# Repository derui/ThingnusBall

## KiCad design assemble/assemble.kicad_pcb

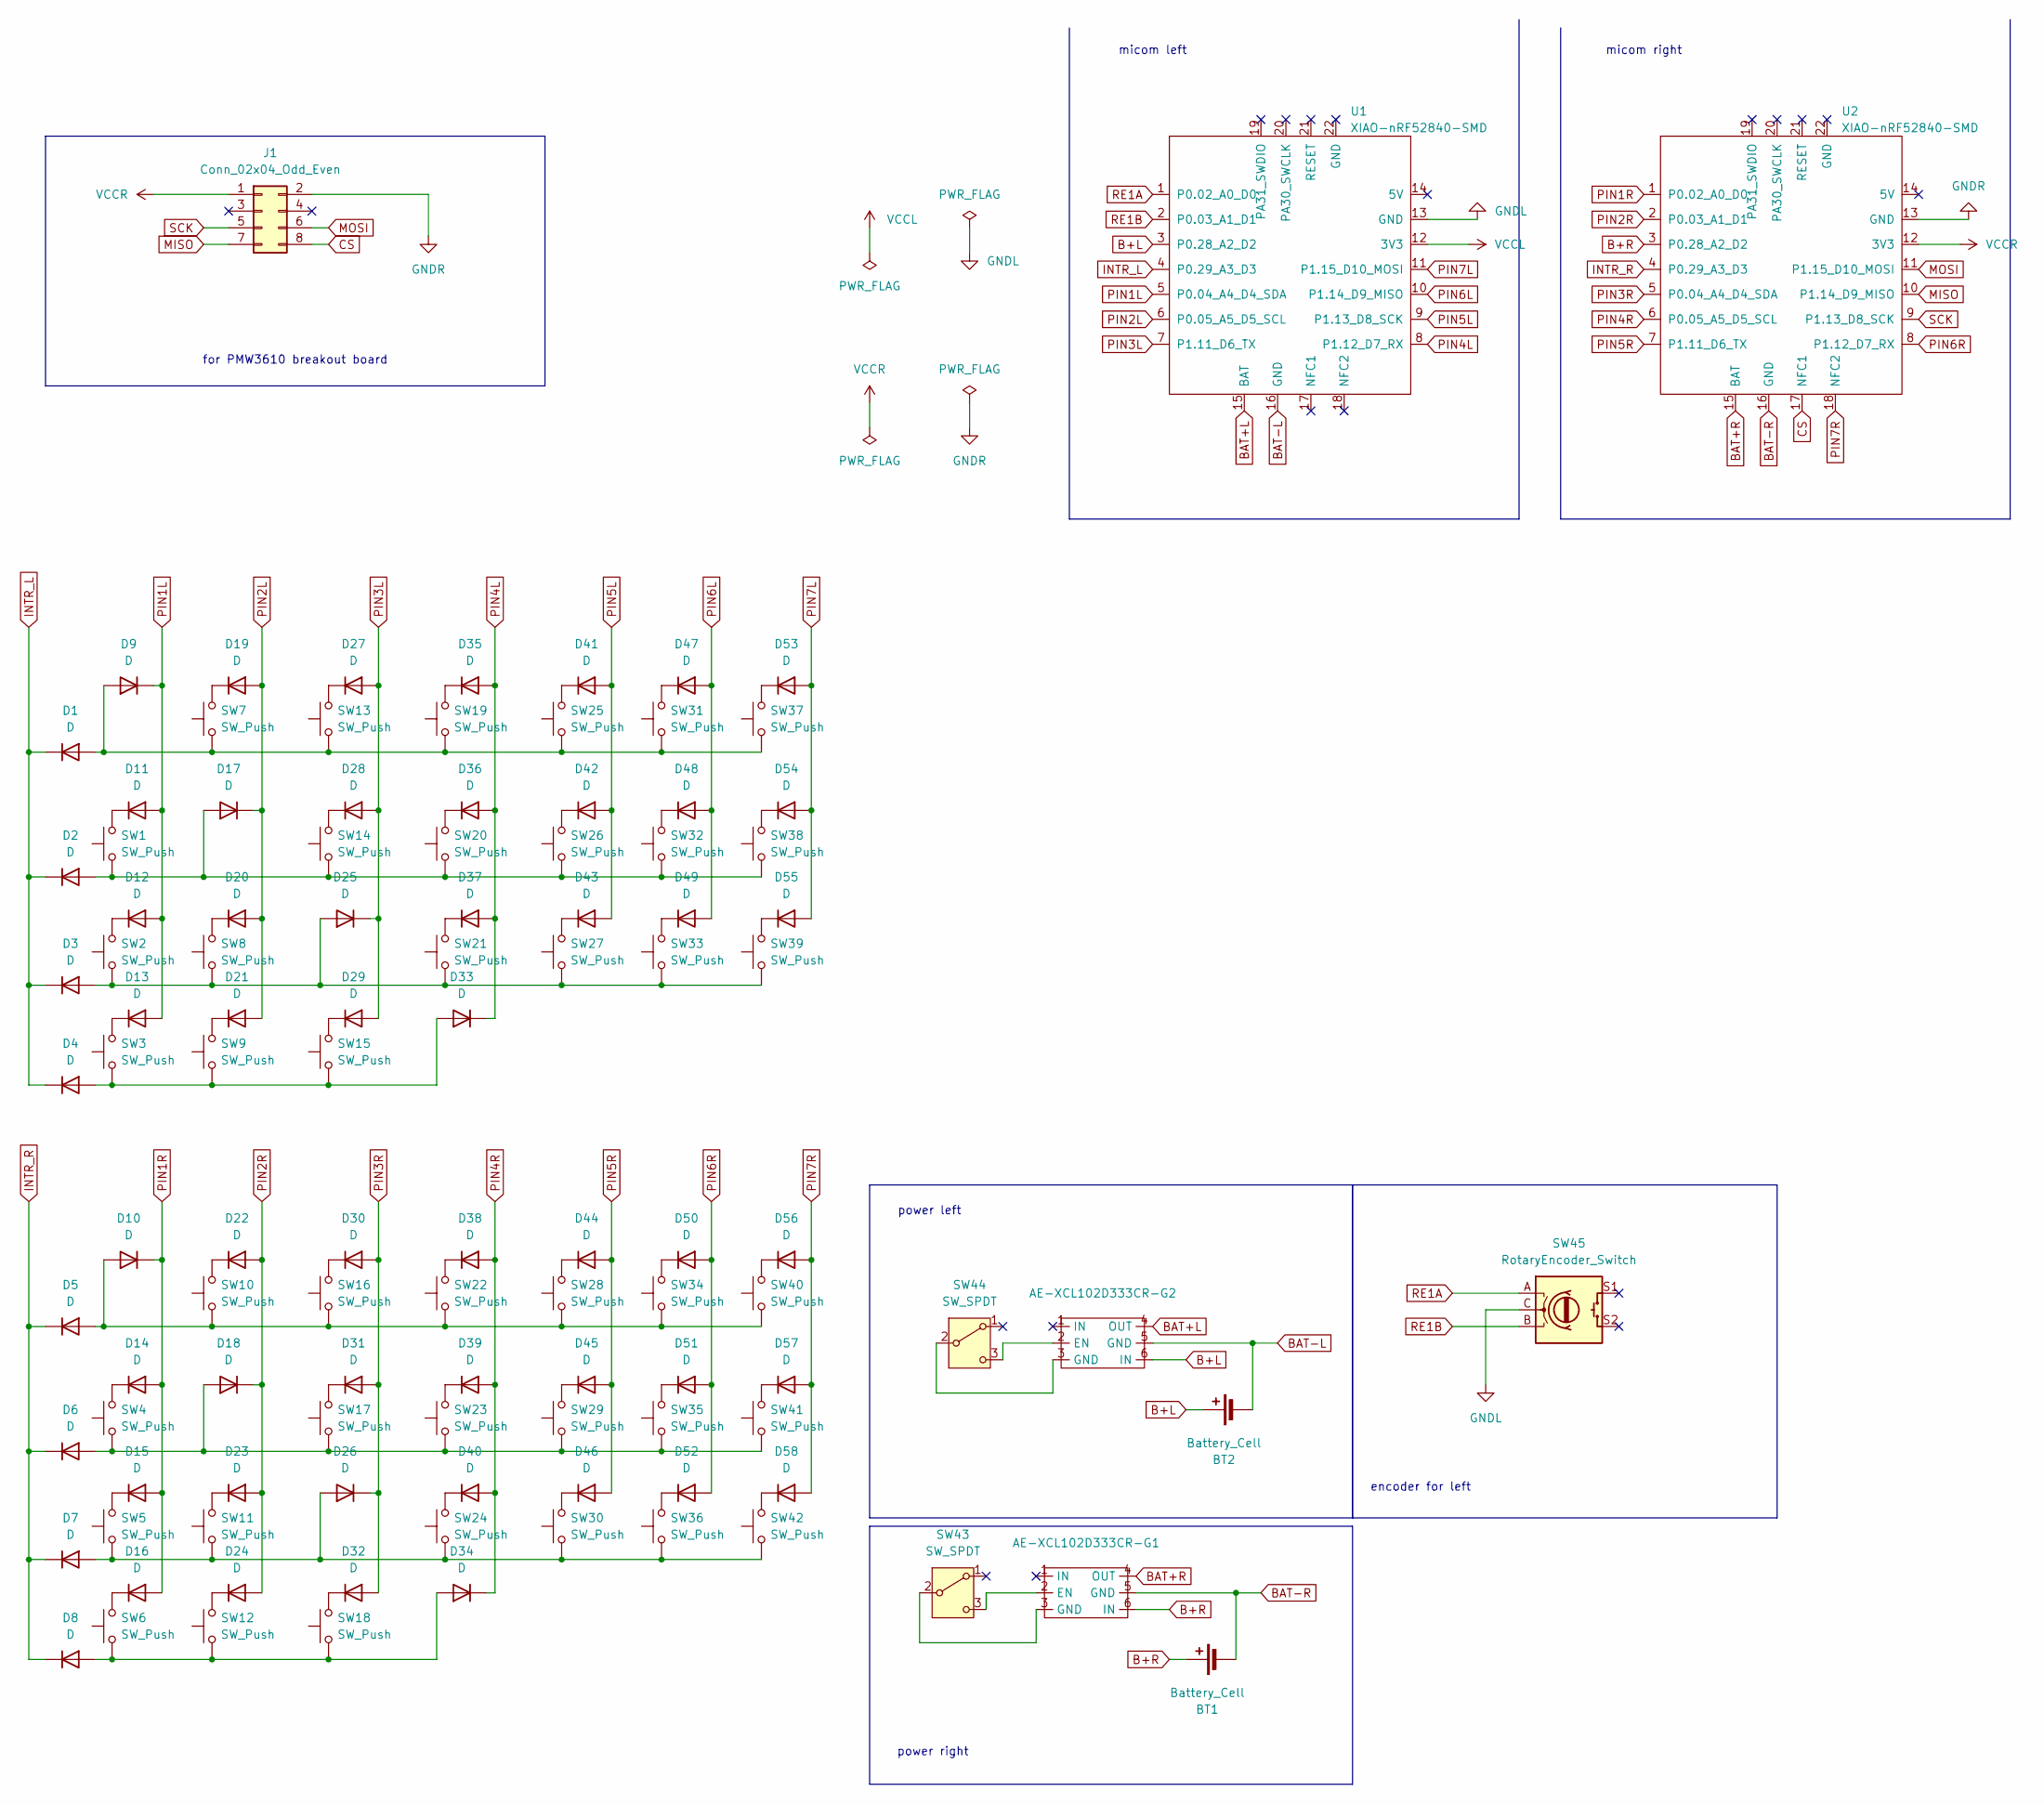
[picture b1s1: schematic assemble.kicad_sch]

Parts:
AE-XCL102D333CR-G1, AE-XCL102D333CR-G2: AE-XCL102D333CR-G
BT1, BT2: Battery_Cell; BatteryHolder_Keystone_2460_1xAA
D1, D2, D3, D4, D5, D6, D7, D8, D9, D10, D11, D12, D13, D14, D15, D16, D17, D18, D19, D20, D21, D22, D23, D24, D25, D26, D27, D28, D29, D30, D31, D32, D33, D34, D35, D36, D37, D38, D39, D40, D41, D42, D43, D44, D45, D46, D47, D48, D49, D50, D51, D52, D53, D54, D55, D56, D57, D58: D; Diode_SMD
J1: Conn_02x04_Odd_Even; PinSocket_2x04_P2.54mm_Vertical
SW1, SW2, SW3, SW4, SW5, SW6, SW7, SW8, SW9, SW10, SW11, SW12, SW13, SW14, SW15, SW16, SW17, SW18, SW19, SW20, SW21, SW22, SW23, SW24, SW25, SW26, SW27, SW28, SW29, SW30, SW31, SW32, SW33, SW34, SW35, SW36, SW37, SW38, SW39, SW40, SW41, SW42: SW_Push; Choc_v2_Hotswap_1u_16.6
SW43, SW44: SW_SPDT; TGSW_MSK-12D19
SW45: RotaryEncoder_Switch; RotaryEncoder_EC12E
U1, U2: XIAO-nRF52840-SMD

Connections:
B+L: AE-XCL102D333CR-G2.6 (IN), BT2.1 (+), U1.3 (P0.28_A2_D2)
B+R: AE-XCL102D333CR-G1.6 (IN), BT1.1 (+), U2.3 (P0.28_A2_D2)
BAT+L: AE-XCL102D333CR-G2.4 (OUT), U1.15 (BAT)
BAT+R: AE-XCL102D333CR-G1.4 (OUT), U2.15 (BAT)
BAT-L: AE-XCL102D333CR-G2.5 (GND), BT2.2 (-), U1.16 (GND)
BAT-R: AE-XCL102D333CR-G1.5 (GND), BT1.2 (-), U2.16 (GND)
CS: J1.8, U2.17 (NFC1)
GNDL: SW45.C, U1.13 (GND)
GNDR: J1.2, U2.13 (GND)
INTR_L: D1.1 (K), D2.1 (K), D3.1 (K), D4.1 (K), U1.4 (P0.29_A3_D3)
INTR_R: D5.1 (K), D6.1 (K), D7.1 (K), D8.1 (K), U2.4 (P0.29_A3_D3)
MISO: J1.7, U2.10 (P1.14_D9_MISO)
MOSI: J1.6, U2.11 (P1.15_D10_MOSI)
unnamed: AE-XCL102D333CR-G1.2 (EN), SW43.3 (C)
unnamed: AE-XCL102D333CR-G2.2 (EN), SW44.3 (C)
unnamed: D1.2 (A), D9.2 (A), SW7.1, SW13.1, SW19.1, SW25.1, SW31.1, SW37.1
unnamed: D5.2 (A), D10.2 (A), SW10.1, SW16.1, SW22.1, SW28.1, SW34.1, SW40.1
unnamed: D11.1 (K), SW1.2
unnamed: D12.1 (K), SW2.2
unnamed: D13.1 (K), SW3.2
unnamed: D14.1 (K), SW4.2
unnamed: D15.1 (K), SW5.2
unnamed: D16.1 (K), SW6.2
unnamed: D2.2 (A), D17.2 (A), SW1.1, SW14.1, SW20.1, SW26.1, SW32.1, SW38.1
unnamed: D6.2 (A), D18.2 (A), SW4.1, SW17.1, SW23.1, SW29.1, SW35.1, SW41.1
unnamed: D19.1 (K), SW7.2
unnamed: D20.1 (K), SW8.2
unnamed: D21.1 (K), SW9.2
unnamed: D22.1 (K), SW10.2
unnamed: D23.1 (K), SW11.2
unnamed: D24.1 (K), SW12.2
unnamed: D3.2 (A), D25.2 (A), SW2.1, SW8.1, SW21.1, SW27.1, SW33.1, SW39.1
unnamed: D7.2 (A), D26.2 (A), SW5.1, SW11.1, SW24.1, SW30.1, SW36.1, SW42.1
unnamed: D27.1 (K), SW13.2
unnamed: D28.1 (K), SW14.2
unnamed: D29.1 (K), SW15.2
unnamed: D30.1 (K), SW16.2
unnamed: D31.1 (K), SW17.2
unnamed: D32.1 (K), SW18.2
unnamed: D4.2 (A), D33.2 (A), SW3.1, SW9.1, SW15.1
unnamed: D8.2 (A), D34.2 (A), SW6.1, SW12.1, SW18.1
unnamed: D35.1 (K), SW19.2
unnamed: D36.1 (K), SW20.2
unnamed: D37.1 (K), SW21.2
unnamed: D38.1 (K), SW22.2
unnamed: D39.1 (K), SW23.2
unnamed: D40.1 (K), SW24.2
unnamed: D41.1 (K), SW25.2
unnamed: D42.1 (K), SW26.2
unnamed: D43.1 (K), SW27.2
unnamed: D44.1 (K), SW28.2
unnamed: D45.1 (K), SW29.2
unnamed: D46.1 (K), SW30.2
unnamed: D47.1 (K), SW31.2
unnamed: D48.1 (K), SW32.2
unnamed: D49.1 (K), SW33.2
unnamed: D50.1 (K), SW34.2
unnamed: D51.1 (K), SW35.2
unnamed: D52.1 (K), SW36.2
unnamed: D53.1 (K), SW37.2
unnamed: D54.1 (K), SW38.2
unnamed: D55.1 (K), SW39.2
unnamed: D56.1 (K), SW40.2
unnamed: D57.1 (K), SW41.2
unnamed: D58.1 (K), SW42.2
unnamed: AE-XCL102D333CR-G1.3 (GND), SW43.2 (B)
unnamed: AE-XCL102D333CR-G2.3 (GND), SW44.2 (B)
PIN1L: D9.1 (K), D11.2 (A), D12.2 (A), D13.2 (A), U1.5 (P0.04_A4_D4_SDA)
PIN1R: D10.1 (K), D14.2 (A), D15.2 (A), D16.2 (A), U2.1 (P0.02_A0_D0)
PIN2L: D17.1 (K), D19.2 (A), D20.2 (A), D21.2 (A), U1.6 (P0.05_A5_D5_SCL)
PIN2R: D18.1 (K), D22.2 (A), D23.2 (A), D24.2 (A), U2.2 (P0.03_A1_D1)
PIN3L: D25.1 (K), D27.2 (A), D28.2 (A), D29.2 (A), U1.7 (P1.11_D6_TX)
PIN3R: D26.1 (K), D30.2 (A), D31.2 (A), D32.2 (A), U2.5 (P0.04_A4_D4_SDA)
PIN4L: D33.1 (K), D35.2 (A), D36.2 (A), D37.2 (A), U1.8 (P1.12_D7_RX)
PIN4R: D34.1 (K), D38.2 (A), D39.2 (A), D40.2 (A), U2.6 (P0.05_A5_D5_SCL)
PIN5L: D41.2 (A), D42.2 (A), D43.2 (A), U1.9 (P1.13_D8_SCK)
PIN5R: D44.2 (A), D45.2 (A), D46.2 (A), U2.7 (P1.11_D6_TX)
PIN6L: D47.2 (A), D48.2 (A), D49.2 (A), U1.10 (P1.14_D9_MISO)
PIN6R: D50.2 (A), D51.2 (A), D52.2 (A), U2.8 (P1.12_D7_RX)
PIN7L: D53.2 (A), D54.2 (A), D55.2 (A), U1.11 (P1.15_D10_MOSI)
PIN7R: D56.2 (A), D57.2 (A), D58.2 (A), U2.18 (NFC2)
RE1A: SW45.A, U1.1 (P0.02_A0_D0)
RE1B: SW45.B, U1.2 (P0.03_A1_D1)
SCK: J1.5, U2.9 (P1.13_D8_SCK)
VCCL: U1.12 (3V3)
VCCR: J1.1, U2.12 (3V3)

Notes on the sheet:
for PMW3610 breakout board
encoder for left
micom right
power left
power right
micom left

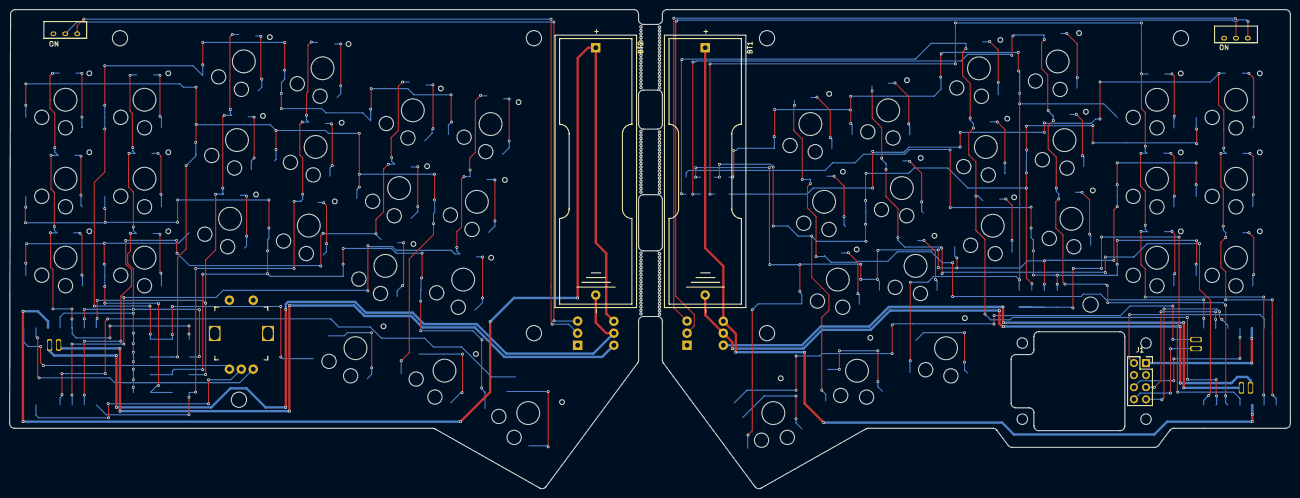
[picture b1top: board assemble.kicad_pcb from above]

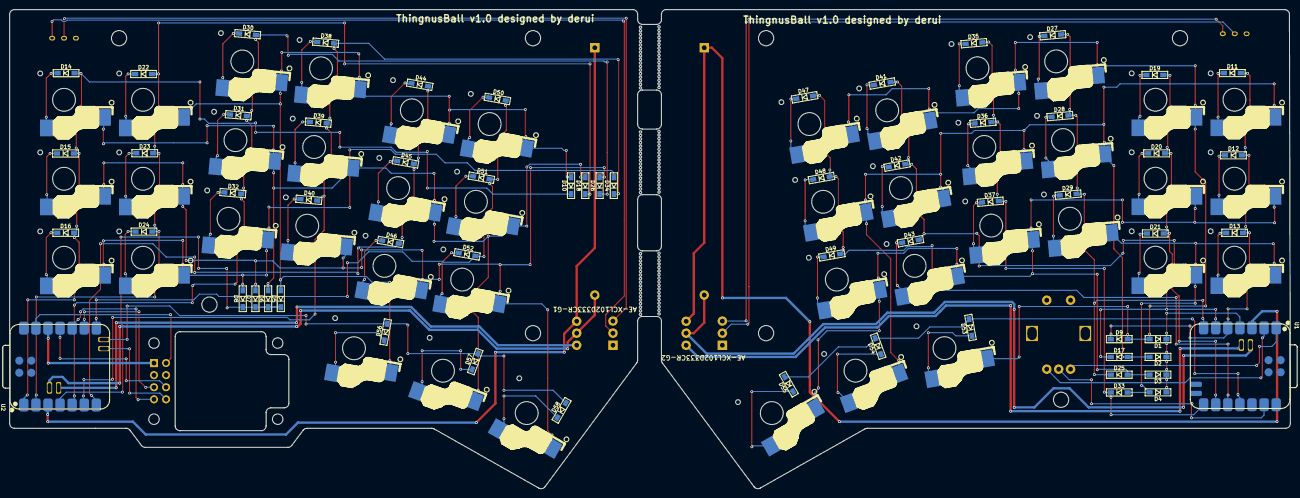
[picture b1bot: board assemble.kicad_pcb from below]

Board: 2 copper layers, 269.2 x 100.7 mm, 140 parts (4 on the bottom side), 85 nets.

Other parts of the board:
Ref**: Val**; Mouse_Bite_Hole
Ref**#2, Ref**#3, Ref**#5, Ref**#6, Ref**#7, Ref**#9, Ref**#17, Ref**#28: Val**; m3_Screw_Hole_EdgeCuts
Ref**#4, Ref**#10, Ref**#12, Ref**#13, Ref**#14, Ref**#15, Ref**#16, Ref**#18, Ref**#19, Ref**#20, Ref**#21, Ref**#22, Ref**#24, Ref**#25, Ref**#27, Ref**#29, Ref**#30: Val**; Mouse_Bite_Hole
Ref**#8, Ref**#11, Ref**#23, Ref**#26: Val**; m2_Screw_Hole_EdgeCuts

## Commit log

2025-09-27 chore: add flake
2025-09-27 chore: add nixpkgs
2025-10-04 feat: WIP assemble
2025-10-11 chore: update flake
2025-10-11 feat: implement PCB
2025-10-13 feat: finish implement PCB
2025-10-13 feat: add switch plate
2025-10-13 doc: change readme
2025-10-13 [ci skip] docs: update LICENSE
2025-10-26 fix: change position
2025-10-27 feat: add bottom plate
2025-10-27 chore: ignore backups
2025-10-28 feat: add case model
2025-11-03 feat: change case and re-wired
2025-11-03 feat: add key cap and trackball
2025-11-03 chore: ignore FCBak
2025-11-03 [ci skip] docs: add BOM temporary
2025-11-08 fix: case problems
2025-11-18 fix: case and cover
2025-11-22 fix: switch cover
